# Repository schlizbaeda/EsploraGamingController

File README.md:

# Arduino Esplora Gaming Controller

This Arduino sketch emulates a mouse and a keyboard subset to work as a
USB gaming controller for a PC using the [Arduino Esplora board](https://store.arduino.cc/arduino-esplora).

It was inspired by the original Arduino sketch [Esplora Joystick Mouse](https://www.arduino.cc/en/Tutorial/EsploraJoystickMouse)
and for the keyboard part by [Esplora Kart](https://www.arduino.cc/en/Tutorial/EsploraKart).
The implementation of the TinkerKit connectors was discovered at [github.com/circuit69/EsploraTinkerkit](https://github.com/circuit69/EsploraTinkerkit)

## Implemented Features
* smooth mouse movement with joystick using binary fixed-point numbers
* scroll wheel emulation by slider potentiometer
* right mouse click by light sensor
* free keyboard assignments to switches 1-4
* connection of 6 switches at the TinkerKit connectors similar to [EsploraTinkerkit](https://github.com/circuit69/EsploraTinkerkit) 

## Planned Features
* store configuration in the EEPROM
* multi-character commands

## Manual
Use the `Arduino Web Editor` or the `Arduino Desktop IDE` as described
on the [Getting Started](https://www.arduino.cc/en/Guide/HomePage)
section of the official [Arduino web site](https://www.arduino.cc) to
program this sketch into the FLASH memory of the Arduino Esplora board.

An Arduino Esplora board flashed with this sketch emulates a USB mouse
and a USB keyboard. There are eight predefined modes with different key
mappings. The mode is indicated via the Esplora's multi colour LED:
* mode 0: "common 1" - dark white
* mode 1: "MinecraftPi" - red
* mode 2: "t.b.d.: yamuplay" - green
* mode 3: "undefined 3" - yellow
* mode 4: "undefined 4" - blue
* mode 5: "undefined 5" - magenta
* mode 6: "undefined 6" - cyan
* mode 7: "common 2" - white

When pressing the four Arduino switches at the same time the sketch
will enter the config mode. Here the user can choose the key mapping
mode by pressing the switches 1 or 3. To select the chosen mode press
again the four switches at the same time. To avoid an unintended mode
change press switch 2 or 4 at first and then the other switches.

* mode 0: only keyboard emulation
* mode 1: adjusted for MinecraftPi: the switches emulate "sawd" to move the player
* mode 2: reserved for [yamuplay](https://github.com/schlizbaeda/yamuplay) control
* mode 3-6: not defined yet
* mode 7: the switches emulate the cursor keys and the joystick the mouse

## Adjusting the Code
The easiest way to adjust the mouse and keyboard emulation is to edit
the values of the two-dimensional array variable `gl_modeKeycodes` and
to re-flash the Arduino Esplora board.

For keyboard emulation use the ASCII codes or the
[extended keyboard modifiers](https://www.arduino.cc/reference/en/language/functions/usb/keyboard/keyboardmodifiers).
The value 0 means mouse emulation.
The value 255 disables this input device completely.

When the value 0 for mouse emulation is given,
* joystick movement emulates mouse cursor movement
* joystick pressure emulates a left button mouse click
* the light sensor emulates a right button mouse click
* the slider potentiometer emulates the mouse wheel
* the switches emulate nothing!
* the orange TinkerKit switches emulate left/right mouse click
* the white TinkerKit switches emulate nothing!

The analogue input modules like joystick and slider potentiometer
return a 10bit value. This 10bit resolution is used to adjust the speed
of the emulated action. If the slider is moved towards the middle the
scroll wheel emulation is stopped immediately.
The light sensor is treated as a digital input button: Shadowing the
sensor means pressing a button and increasing light intensity means
releasing a button.
The two switches on each white TinkerKit connector are distinguished
by different voltage divider circuits which result in different
analogue values.

## Remarks
* An extended manual is added in the sub directory `latex` in English
  and in German language. A description of this multi lingual
  conception can be found at https://github.com/schlizbaeda/raspiblaster-manual
* The file `Arduino_Esplora_Case.zip` contains 3D printer files of the
  case. They weren't created by me but by JoeyC at 
  https://www.thingiverse.com/thing:45880/
  It is licensed under CC BY-NC 3.0 (no commercial use!)

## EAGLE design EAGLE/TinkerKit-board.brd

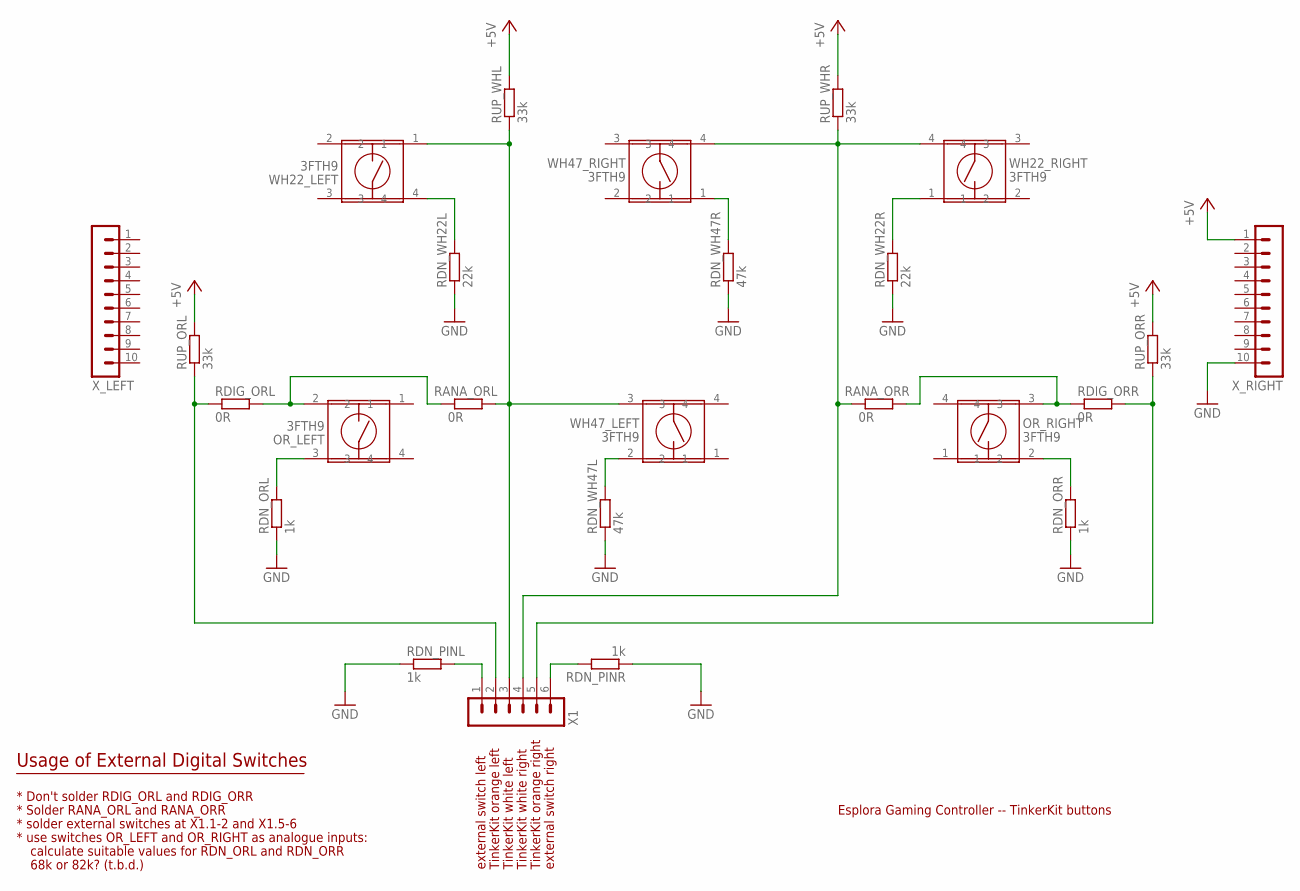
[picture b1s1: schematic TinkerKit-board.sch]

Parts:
OR_LEFT: 3FTH9
OR_RIGHT: 3FTH9
RANA_ORL: 0R; R0603
RANA_ORR: 0R; R0603
RDIG_ORL: 0R; R0603
RDIG_ORR: 0R; R0603
RDN_ORL: 1k; M1206
RDN_ORR: 1k; M1206
RDN_PINL: 1k; R0603
RDN_PINR: 1k; R0603
RDN_WH22L, RDN_WH22R: 22k; M1206
RDN_WH47L, RDN_WH47R: 47k; M1206
RUP_ORL: 33k; M1206
RUP_ORR: 33k; M1206
RUP_WHL: 33k; M1206
RUP_WHR: 33k; M1206
WH22_LEFT, WH22_RIGHT, WH47_LEFT, WH47_RIGHT: 3FTH9
X1: MA06-1
X_LEFT: MA10-1
X_RIGHT: MA10-1

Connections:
+5V: RUP_ORL.2, RUP_ORR.2, RUP_WHL.2, RUP_WHR.2, X_RIGHT.1
GND: RDN_ORL.1, RDN_ORR.1, RDN_PINL.1, RDN_PINR.1, RDN_WH22L.1, RDN_WH22R.1, RDN_WH47L.1, RDN_WH47R.1, X_RIGHT.10
unnamed: OR_LEFT.3, RDN_ORL.2
unnamed: OR_RIGHT.2, RDN_ORR.2
unnamed: RDN_WH22L.2, WH22_LEFT.4
unnamed: RDN_WH47L.2, WH47_LEFT.2
unnamed: RDN_WH22R.2, WH22_RIGHT.1
unnamed: RDN_WH47R.2, WH47_RIGHT.1
unnamed: OR_LEFT.2, RANA_ORL.1, RDIG_ORL.2
unnamed: OR_RIGHT.3, RANA_ORR.2, RDIG_ORR.1
ORANGE_LEFT: RDIG_ORL.1, RUP_ORL.1, X1.2
ORANGE_RIGHT: RDIG_ORR.2, RUP_ORR.1, X1.5
PIN_LEFT: RDN_PINL.2, X1.1
PIN_RIGHT: RDN_PINR.2, X1.6
WHITE_LEFT: RANA_ORL.2, RUP_WHL.1, WH22_LEFT.1, WH47_LEFT.3, X1.3
WHITE_RIGHT: RANA_ORR.1, RUP_WHR.1, WH22_RIGHT.4, WH47_RIGHT.4, X1.4

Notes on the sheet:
Esplora Gaming Controller -- TinkerKit buttons
TinkerKit white left
TinkerKit white right
TinkerKit orange right
TinkerKit orange left
external switch left
external switch right
Usage of External Digital Switches
* Don't solder RDIG_ORL and RDIG_ORR
* Solder RANA_ORL and RANA_ORR
* use switches OR_LEFT and OR_RIGHT as analogue inputs:
calculate suitable values for RDN_ORL and RDN_ORR
* solder external switches at X1.1-2 and X1.5-6
68k or 82k? (t.b.d.)

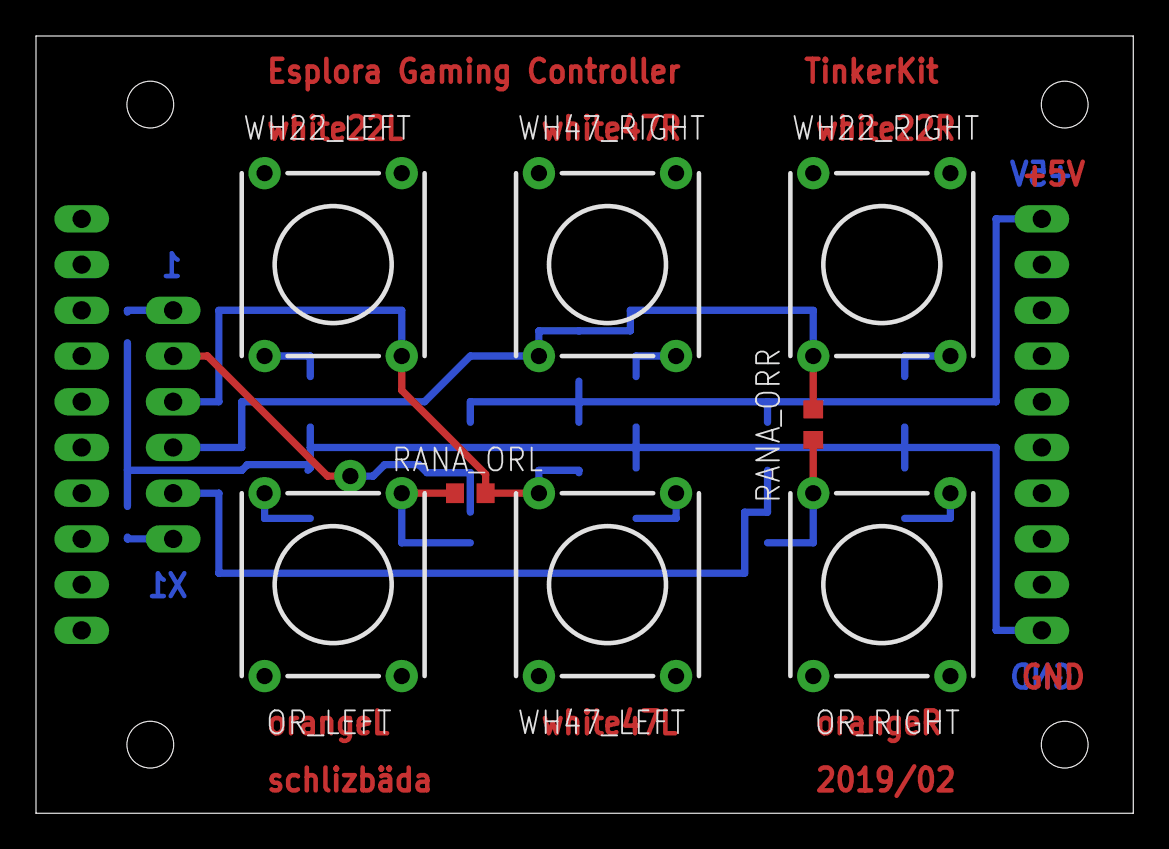
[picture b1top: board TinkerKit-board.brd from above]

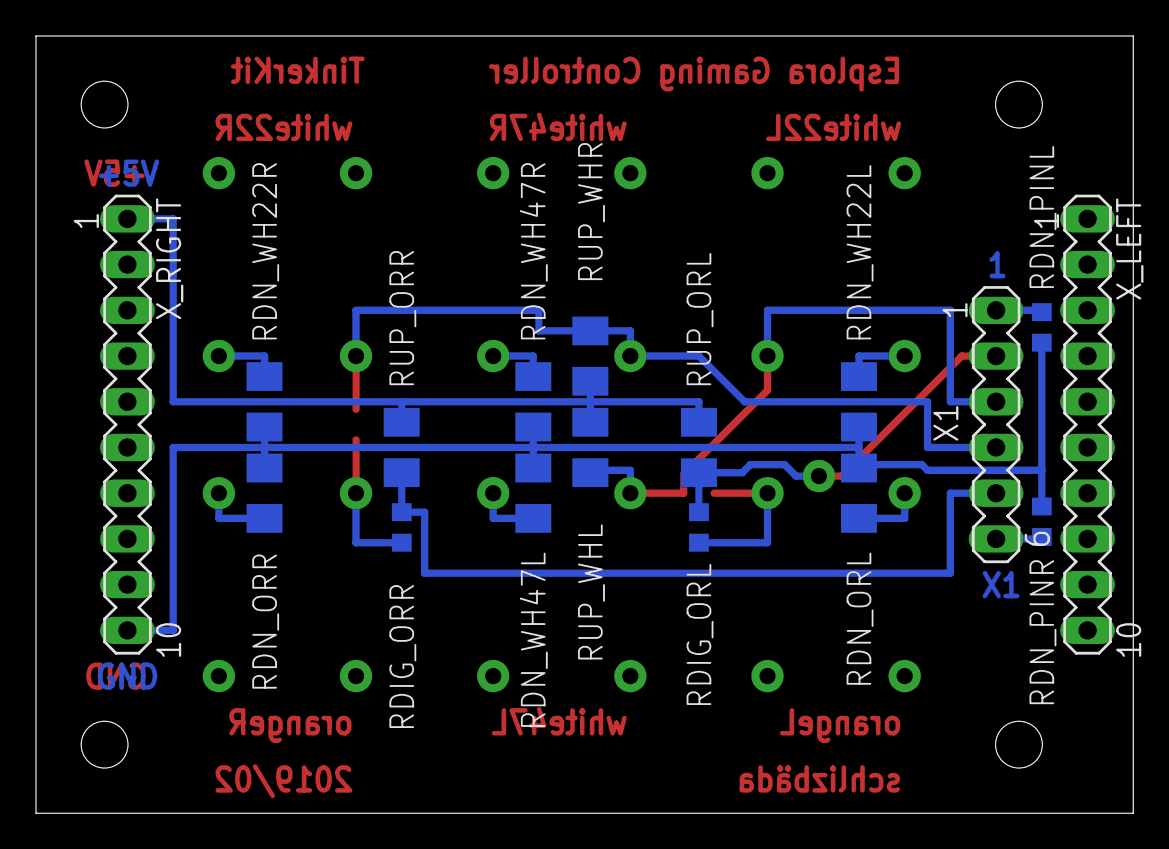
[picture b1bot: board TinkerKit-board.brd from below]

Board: 2 copper layers, 61.0 x 43.2 mm, 26 parts (17 on the bottom side), 16 nets.

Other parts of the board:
U$2: A5L-LOC

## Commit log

2018-12-27 README.md: corrected link format
2018-12-27 Licensed under GNU GPL v3
2019-01-06 implementation of six switches at the TinkerKit connectors
2019-01-27 MinecraftPi settings updated
    After soldering all six TinkerKit push buttons on my additional
    hardware the software was updated to the correct keyboard assignments.
2019-02-08 LaTeX documentation, EAGLE drawings, TinkerKit case
2019-02-08 LaTeX documentation added
2019-02-08 README.md updated
